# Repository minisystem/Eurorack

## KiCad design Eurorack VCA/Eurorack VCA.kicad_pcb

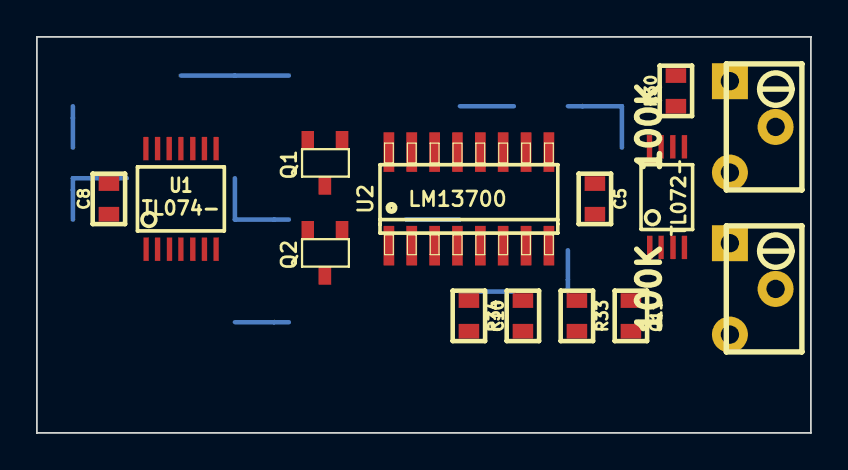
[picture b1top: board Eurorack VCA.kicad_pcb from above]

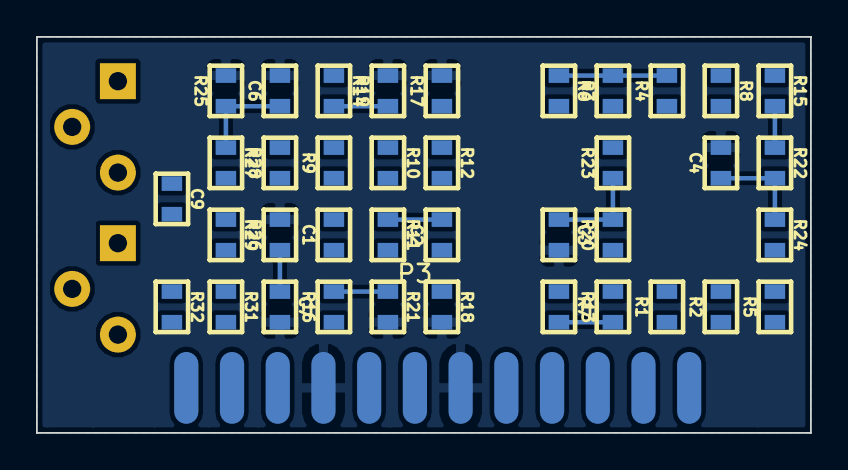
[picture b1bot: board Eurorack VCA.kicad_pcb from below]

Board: 2 copper layers, 43.0 x 22.0 mm, 53 parts (39 on the bottom side), 43 nets.

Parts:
C1, C2, C10, C11: 1μ; SM0603-JRL
C3, C4: 0.1μ; SM0603-JRL
C5, C8, C9: 100n; SM0603-JRL
C6, C7: 47p; SM0603-JRL
P1, P2: 100K; BI_64W_TRIM
P3: CONN_12; CONN_12X_0100_SMD
Q1, Q2: 2N3906; SOT23-JRL
R1, R2, R3, R4, R5, R6, R7, R8, R13, R15, R27, R28, R29, R30: 100K; SM0603-JRL
R9, R11: 82K; SM0603-JRL
R10, R12: 2.2M; SM0603-JRL
R14, R16: 4.7K; SM0603-JRL
R17, R18, R19, R21: 560; SM0603-JRL
R20, R22: 10K; SM0603-JRL
R23, R24: 22K; SM0603-JRL
R25, R26: 47K; SM0603-JRL
R31, R32: 1K; SM0603-JRL
R33, R34: 10; SM0603-JRL
U1: TL074-; TSSOP14
U2: LM13700; SO16-JRL
U3: TL072-; TSSOP8-JRL

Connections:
+12V: C5.1, C8.1, C9.1, C11.1, P1.1, P2.1, R33.1, U1.4, U2.11, U3.8
-12V: C5.2, C8.2, C9.2, C10.2, P1.3, P2.3, R34.1, U1.11, U2.6, U3.4
CV1A: P3.11, R1.1
CV1B: P3.12, R2.1
CV2A: P3.9, R3.1
CV2B: P3.10, R4.1
GND: C3.2, C4.2, C6.2, C7.2, C10.1, C11.2, P3.4, P3.7, Q1.2, Q2.2, R17.2, R18.2, R19.2, R21.2, R25.2, R26.2, U1.3, U1.5, U1.10, U1.12, U3.3, U3.5
IN1: C1.1, P3.6
IN2: C2.1, P3.8
unnamed: R30.2, R32.1, U3.7
unnamed: R8.2, R15.1, U1.13
unnamed: R15.2, R22.1, U1.14
unnamed: Q2.3, U2.1
unnamed: R28.2, R30.1, U3.6
unnamed: R17.1, U2.14
unnamed: R14.2, R19.1, U2.13
unnamed: C4.1, R22.2, R24.1
unnamed: Q2.1, R24.2
unnamed: R3.2, R4.2, R6.1, U1.9
unnamed: R6.2, R8.1, U1.8
unnamed: P3.5, R34.2
unnamed: P3.3, R33.2
unnamed: C7.1, R26.1, R28.1, U2.5
unnamed: C2.2, R11.1
unnamed: P2.2, R12.1
unnamed: R11.2, R12.2, R16.1
unnamed: R16.2, R21.1, U2.4
unnamed: R18.1, U2.3
unnamed: C3.1, R20.2, R23.1
unnamed: Q1.1, R23.2
unnamed: R1.2, R2.2, R5.1, U1.2
unnamed: R5.2, R7.1, U1.1
unnamed: C1.2, R9.1
unnamed: C6.1, R25.1, R27.1, U2.12
unnamed: P1.2, R10.1
unnamed: R9.2, R10.2, R14.1
unnamed: R7.2, R13.1, U1.6
unnamed: R13.2, R20.1, U1.7
unnamed: Q1.3, U2.16
unnamed: R29.2, R31.1, U3.1
unnamed: R27.2, R29.1, U3.2
OUT1: P3.2, R31.2
OUT2: P3.1, R32.2

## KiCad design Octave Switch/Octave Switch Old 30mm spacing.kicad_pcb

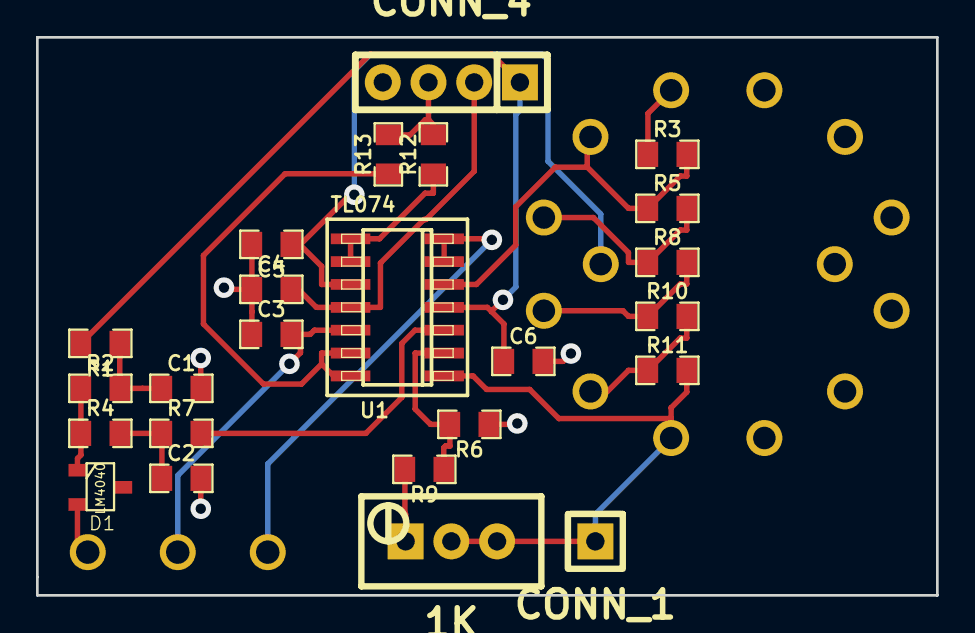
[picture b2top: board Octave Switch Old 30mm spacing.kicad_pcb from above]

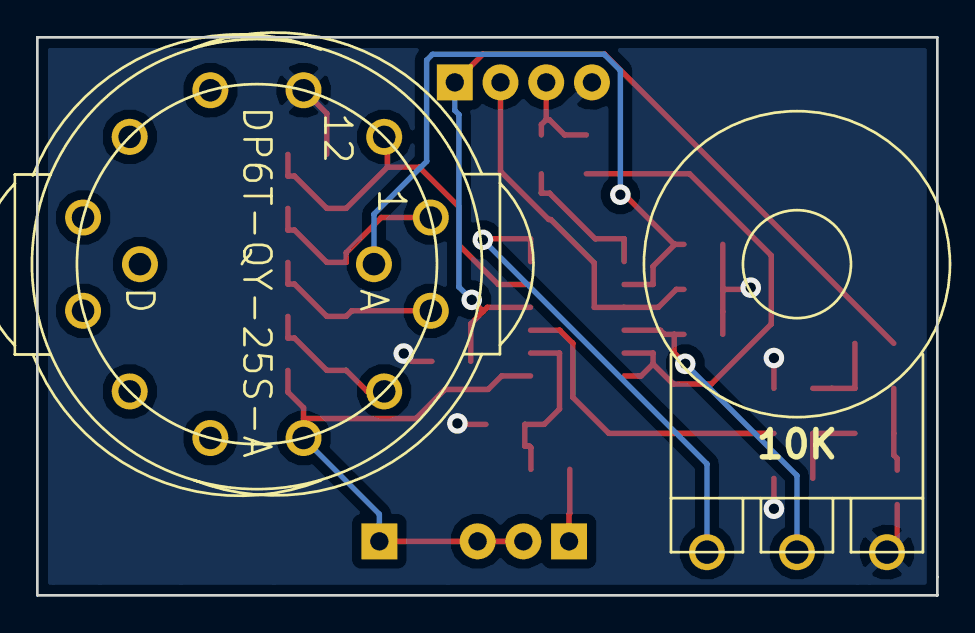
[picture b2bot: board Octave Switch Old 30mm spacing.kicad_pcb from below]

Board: 2 copper layers, 50.0 x 31.0 mm, 26 parts (2 on the bottom side), 20 nets.

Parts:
C1, C2, C4, C6: 0.1u; SM0805-HAND
C3, C5: 0.001u; SM0805-HAND
D1: LM4040; SOT23
P1: CONN_1; CONN_0100_X_1
P2: CONN_4; CONN_0100_X_4
POT1: 10K; RV16A-41
R1, R2: 4.7K; SM0805-HAND
R3, R5, R6, R8, R10, R11: 10K; SM0805-HAND
R4, R7: 33K; SM0805-HAND
R9: 9.53K; SM0805-HAND
R12, R13: 100K; SM0805-HAND
SW1: DP6T-QY-25S-A; QY-25S-2P6C
TRIM1: 1K; BI_67W_TRIM
U1: TL074; -SO14

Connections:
+12V: C6.1, P2.1, R1.2, U1.4
-12V: C4.2, P2.2, U1.11
GND: C1.2, C2.2, C3.1, C4.1, C5.2, C6.2, D1.2, P2.4, POT1.3, R3.1, R6.1, SW1.11
unnamed: D1.1, R2.1, R4.1
unnamed: C1.1, R1.1, R2.2
unnamed: R13.1, U1.13, U1.14
unnamed: C5.1, SW1.A, U1.10
unnamed: R12.1, U1.8, U1.9
unnamed: R7.2, U1.3
unnamed: C2.1, R4.2, R7.1
unnamed: P1.1, R11.2, SW1.4, TRIM1.2, TRIM1.3, U1.1
unnamed: R6.2, R9.1, U1.2
unnamed: R9.2, TRIM1.1
unnamed: R10.2, R11.1, SW1.3
unnamed: R3.2, R5.1, SW1.12, U1.5
unnamed: R8.2, R10.1, SW1.2
unnamed: R5.2, R8.1, SW1.1
unnamed: POT1.1, U1.6, U1.7
unnamed: C3.2, POT1.2, U1.12
SUM OUT: P2.3, R12.2, R13.2
